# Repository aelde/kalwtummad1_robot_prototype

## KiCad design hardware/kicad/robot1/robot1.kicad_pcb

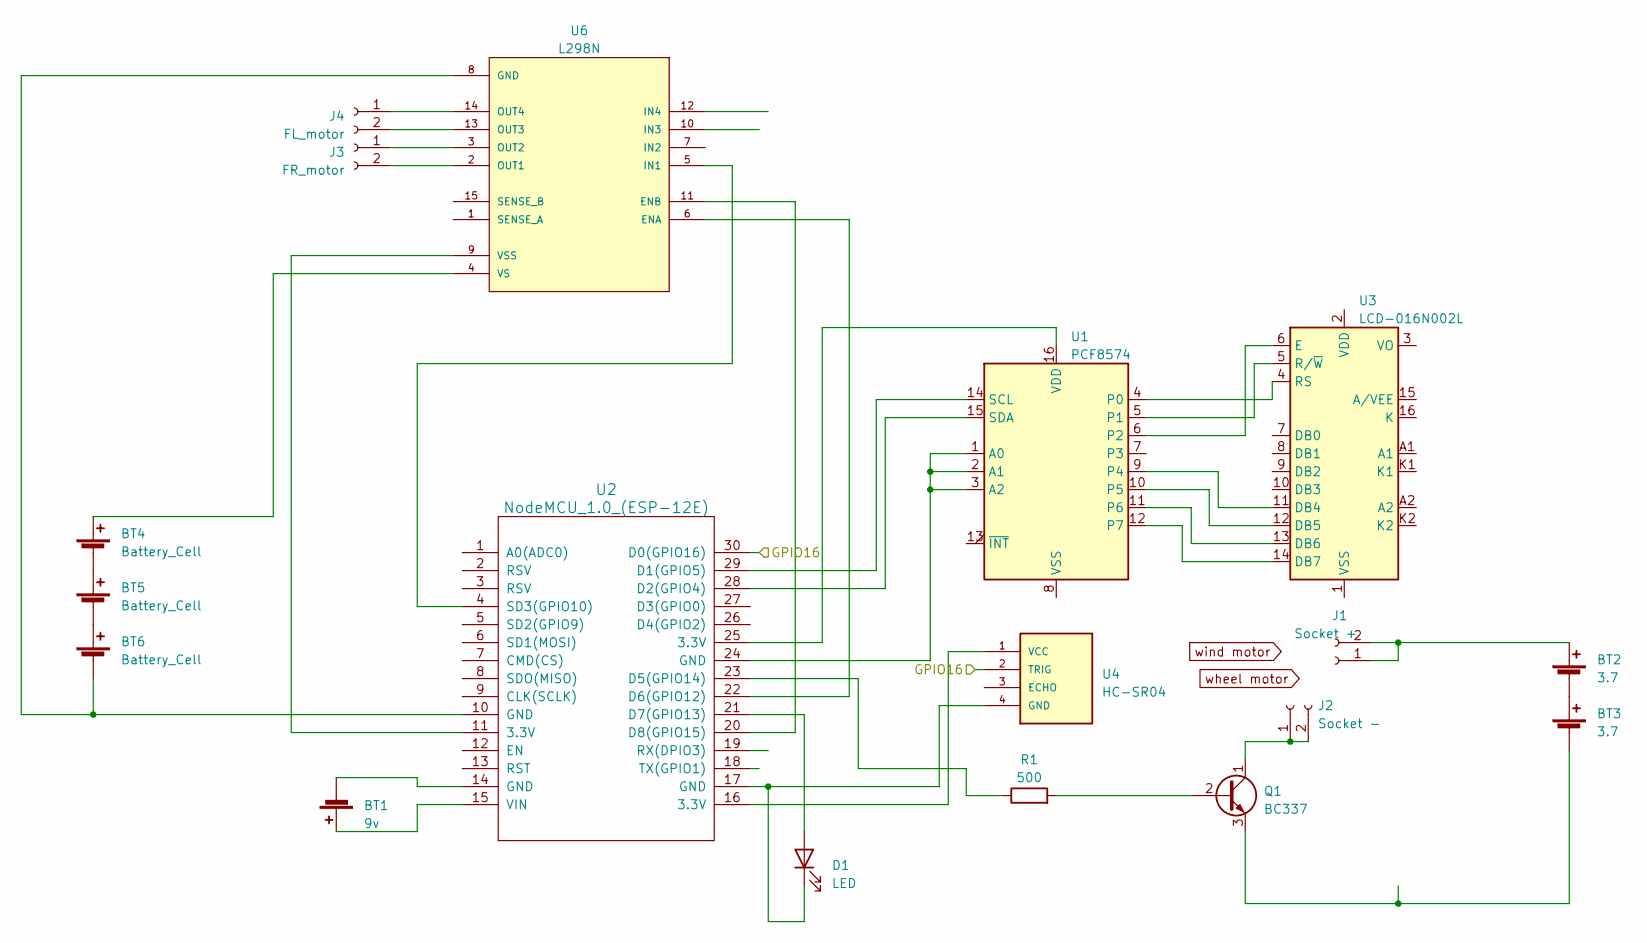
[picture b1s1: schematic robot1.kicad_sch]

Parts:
BT1: 9v; BatteryHolder_Eagle_12BH611-GR
BT2, BT3: 3.7; BatteryHolder_Keystone_1042_1x18650
BT4, BT5, BT6: Battery_Cell; BatteryHolder_Keystone_1042_1x18650
D1: LED; LED_D3.0mm_Horizontal_O1.27mm_Z2.0mm
J1: Socket +; PinSocket_1x02_P1.00mm_Vertical_SMD_Pin1Left
J2: Socket -; PinSocket_1x02_P1.00mm_Vertical_SMD_Pin1Left
J3: FR_motor; PinSocket_1x02_P1.00mm_Vertical_SMD_Pin1Left
J4: FL_motor; PinSocket_1x02_P1.00mm_Vertical_SMD_Pin1Left
Q1: BC337; TO-92_Inline
R1: 500; R_Axial_DIN0204_L3.6mm_D1.6mm_P2.54mm_Vertical
U1: PCF8574; DIL16
U2: NodeMCU_1.0_(ESP-12E); NodeMCU-LoLinV3
U3: LCD-016N002L
U4: HC-SR04
U6: L298N; TO-220-15_P2.54x2.54mm_StaggerEven_Lead4.58mm_Vertical

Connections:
unnamed: BT1.1 (+), U2.15 (VIN)
unnamed: BT1.2 (-), U2.14 (GND)
unnamed: BT2.1 (+), J1.1, J1.2
unnamed: BT2.2 (-), BT3.1 (+)
unnamed: BT3.2 (-), Q1.3 (E)
unnamed: BT4.1 (+), U6.4 (VS)
unnamed: BT4.2 (-), BT5.1 (+)
unnamed: BT5.2 (-), BT6.1 (+)
unnamed: BT6.2 (-), U2.10 (GND), U6.8 (GND)
unnamed: D1.2 (A), U2.21 (D7(GPIO13))
unnamed: D1.1 (K), U2.17 (GND), U4.4 (GND)
unnamed: J2.1, J2.2, Q1.1 (C)
unnamed: J3.1, U6.3 (OUT2)
unnamed: J3.2, U6.2 (OUT1)
unnamed: J4.1, U6.14 (OUT4)
unnamed: J4.2, U6.13 (OUT3)
unnamed: Q1.2 (B), R1.2
unnamed: U1.1 (A0), U1.2 (A1), U1.3 (A2), U2.24 (GND)
unnamed: U1.4 (P0), U3.4 (RS)
unnamed: U1.5 (P1), U3.5 (R/~W)
unnamed: U1.6 (P2), U3.6 (E)
unnamed: U1.9 (P4), U3.11 (DB4)
unnamed: U1.10 (P5), U3.12 (DB5)
unnamed: U1.11 (P6), U3.13 (DB6)
unnamed: U1.12 (P7), U3.14 (DB7)
unnamed: U1.14 (SCL), U2.29 (D1(GPIO5))
unnamed: U1.15 (SDA), U2.28 (D2(GPIO4))
unnamed: U1.16 (VDD), U2.25 (3.3V)
unnamed: U2.27 (D3(GPIO0)), U4.3 (ECHO)
unnamed: R1.1, U2.23 (D5(GPIO14))
unnamed: U2.22 (D6(GPIO12)), U6.6 (ENA)
unnamed: U2.20 (D8(GPIO15)), U6.11 (ENB)
unnamed: U2.19 (RX(DPIO3)), U6.12 (IN4)
unnamed: U2.4 (SD3(GPIO10)), U6.5 (IN1)
unnamed: U2.18 (TX(GPIO1)), U6.10 (IN3)
unnamed: U2.16 (3.3V), U4.1 (VCC)
unnamed: U2.11 (3.3V), U6.9 (VSS)

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
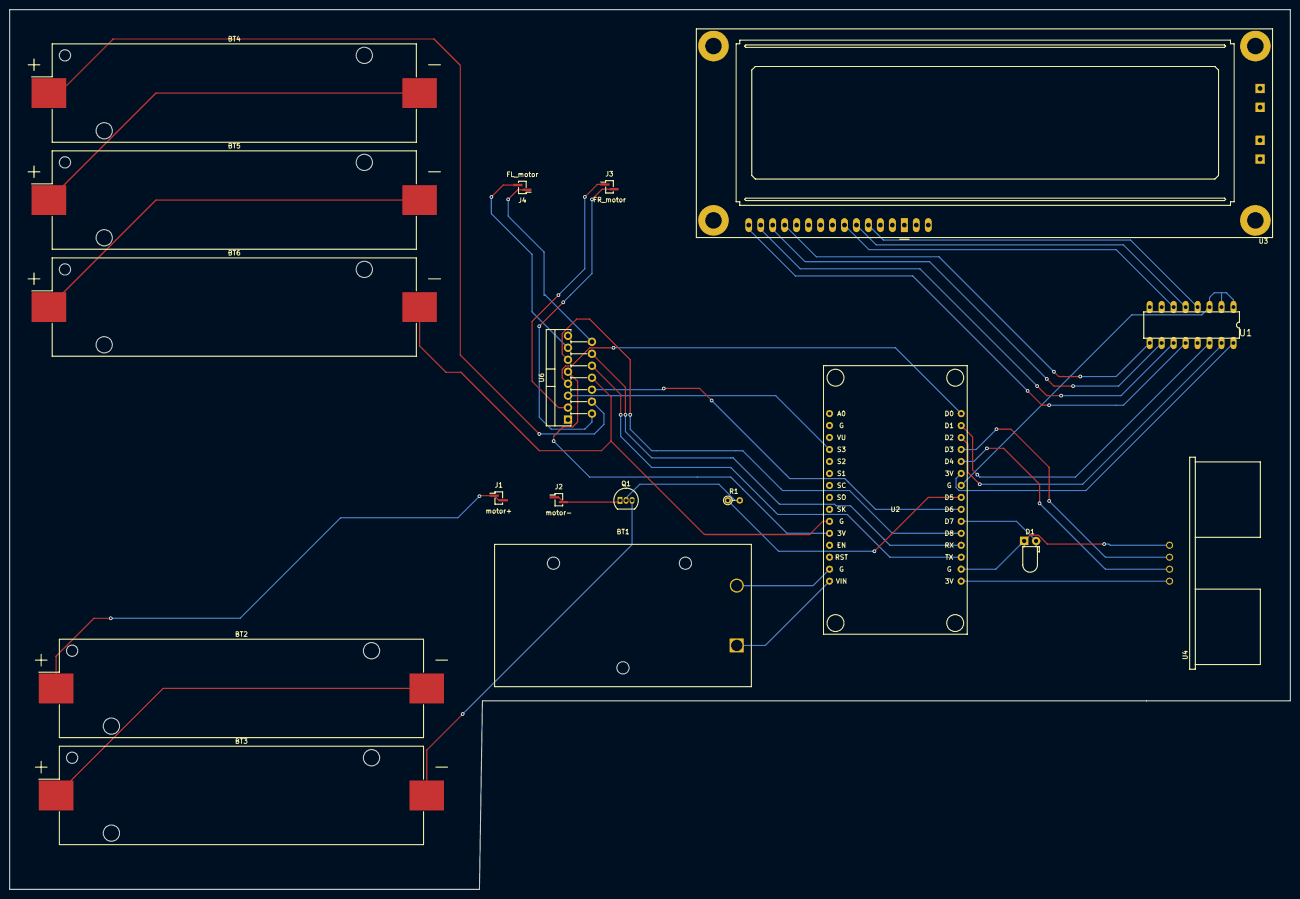
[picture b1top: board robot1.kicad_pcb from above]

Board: 2 copper layers, 271.8 x 186.7 mm, 18 parts (0 on the bottom side), 39 nets.
